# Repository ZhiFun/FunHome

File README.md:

# FunHome
DIY design of smart home hardware based on Home Assistant.
It will include a variety of DIY smart home hardware: smart lights, smart switches, various sensors, automation devices, etc., and will be continuously updated.

  a. Provides CAD files for direct 3D printing.
  
  b. Offers hardware design for PCB fabrication.
  
  c. Provides YAML configuration code for configuring corresponding functions in ESPHome.
  
  (for usage instructions, refer to:https://www.bilibili.com/video/BV14ryhYHEJK/?spm_id_from=333.999.0.0&vd_source=eef55077bd933049fd878e3b9b8782e2) 

【1】 funHomeLight：
A night light based on ESP32-C3 + WS2812 + DS18B20, capable of displaying multiple colors, various display effects, timed on/off, temperature protection, and other features.

cad: https://a360.co/3APonfi

【2】funHomeSensorTH：
The funHomeSensorTH is based on the ESP32-C3 + DHT11 and integrates temperature and humidity data acquisition functionality, with configurable reporting frequency.

cad: https://a360.co/3CE3DYF

【3】funHomeSwitch：
funHomeSwitch is composed of modules such as the ES32C3, SG90 servo, ambient light sensor, lithium battery, etc. It can be installed on a standard 86-type switch and used with Home Assistant for remote light control.

cad: https://a360.co/4gaNJ6r

【4】funHomeFan：
The funHomeFan is an intelligent small fan project based on the ESP32C3, which can be remotely controlled via a smartphone to adjust the fan speed with 3 adjustable levels.

cad: https://a360.co/4jmC1qw

【5】funHomePcController：
The funHomePcController is based on the ESP32-C3 and allows one-click remote control of a computer’s power on/off, with support for low power consumption.

cad: https://a360.co/3GjO7Dl

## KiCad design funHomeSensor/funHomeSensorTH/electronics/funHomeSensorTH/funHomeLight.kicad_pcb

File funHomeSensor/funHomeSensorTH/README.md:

The project is based on ESPHome and applied to the Home Assistant platform.

cad:
https://a360.co/3CE3DYF

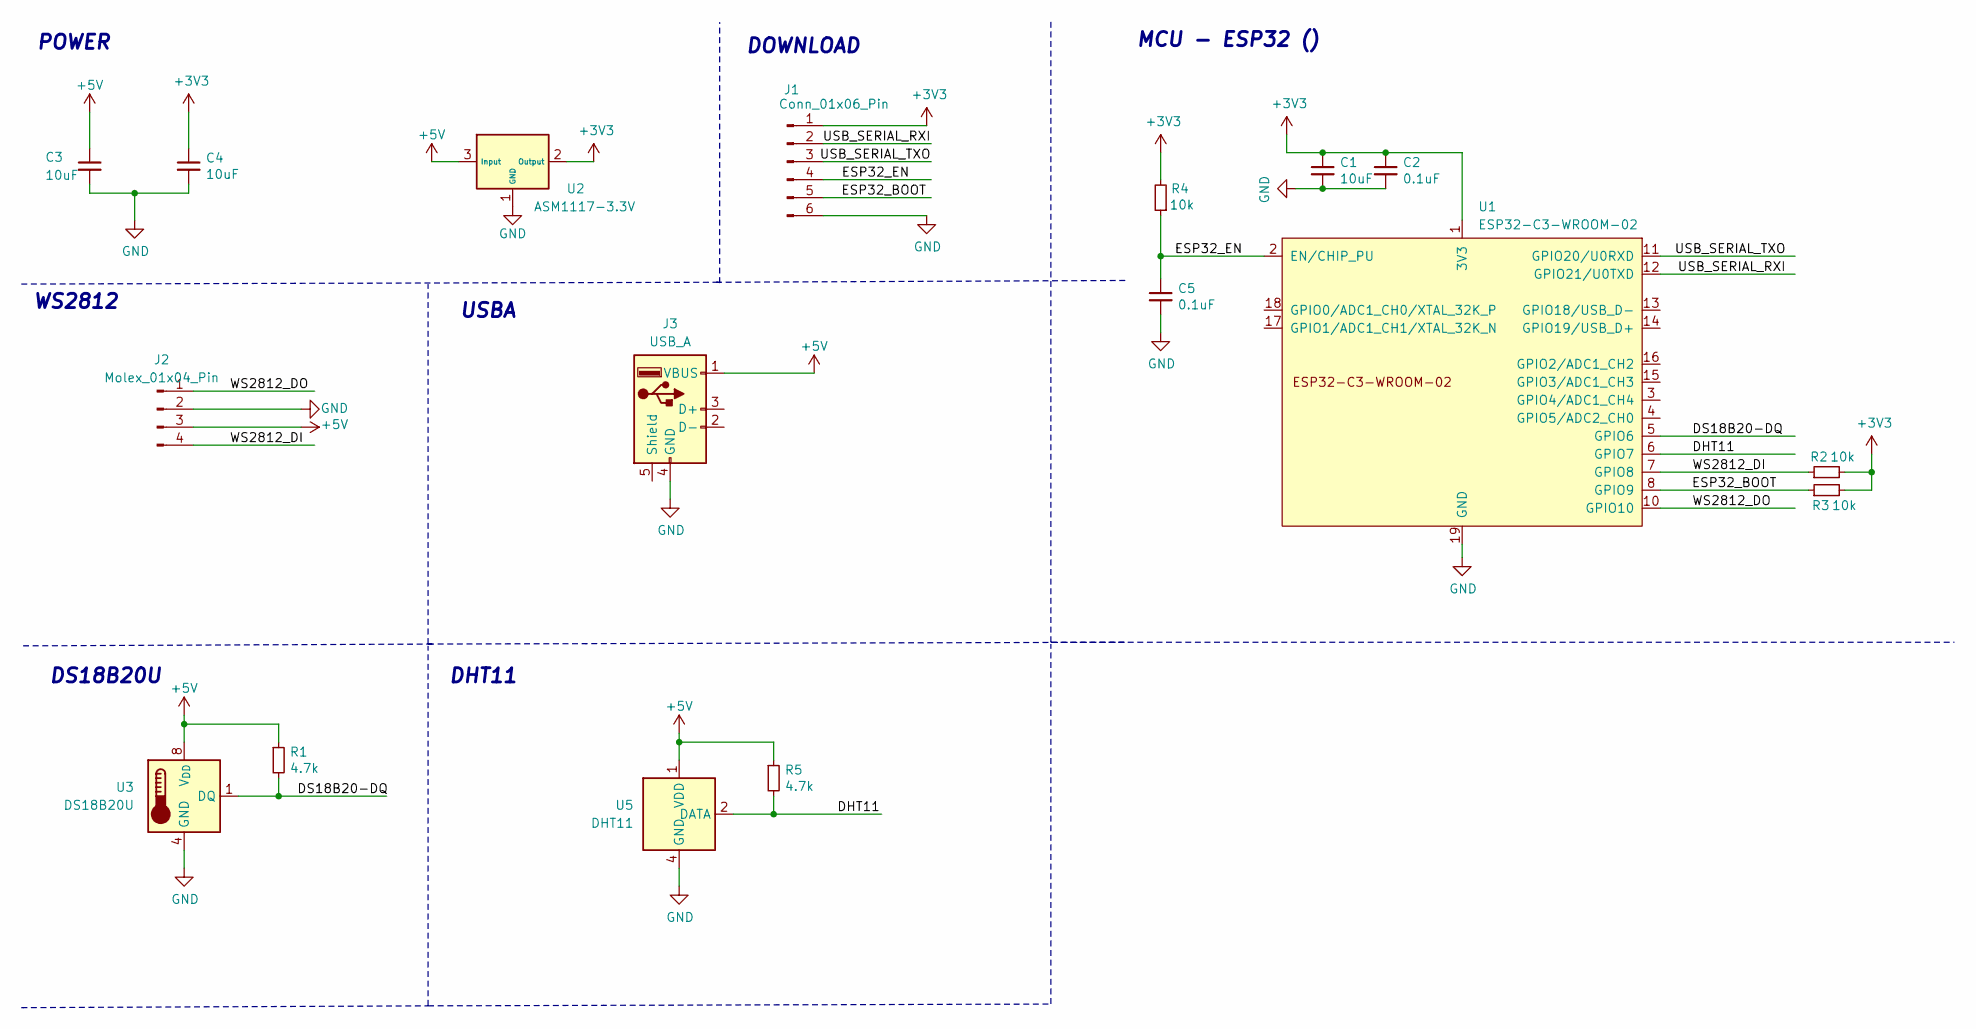
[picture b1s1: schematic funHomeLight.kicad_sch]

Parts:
C1, C3, C4: 10uF; C_0805_2012Metric; LCSC C15850
C2, C5: 0.1uF; C_0805_2012Metric; LCSC C1591
J1: Conn_01x06_Pin; JST_XH_B6B-XH-A_1x06_P2.50mm_Vertical
J2: Molex_01x04_Pin; Molex_CLIK-Mate_502382-0470_1x04-1MP_P1.25mm_Vertical
J3: USB_A; USB_A_Molex_105057_Vertical
R1, R5: 4.7k; R_0603_1608Metric; LCSC C105580
R2, R3, R4: 10k; R_0603_1608Metric; LCSC C105580
U1: ESP32-C3-WROOM-02
U2: ASM1117-3.3V; SOT-223-3_TabPin2; LCSC C6186, C35879, or others
U3: DS18B20U; MSOP-8_3x3mm_P0.65mm
U5: DHT11; Aosong_DHT11_5.5x12.0_P2.54mm

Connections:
+3V3: C1.1, C2.1, C4.1, J1.1, R2.2, R3.2, R4.2, U1.1 (3V3), U2.2 (Output)
+5V: C3.1, J2.3, J3.1 (VBUS), R1.1, R5.1, U2.3 (Input), U3.8 (V_{DD}), U5.1 (VDD)
/DHT11: R5.2, U1.6 (GPIO7), U5.2 (DATA)
/DS18B20-DQ: R1.2, U1.5 (GPIO6), U3.1 (DQ)
/ESP32_BOOT: J1.5, R3.1, U1.8 (GPIO9)
/ESP32_EN: C5.1, J1.4, R4.1, U1.2 (EN/CHIP_PU)
/USB_SERIAL_RXI: J1.2, U1.12 (GPIO21/U0TXD)
/USB_SERIAL_TXO: J1.3, U1.11 (GPIO20/U0RXD)
/WS2812_DI: J2.4, R2.1, U1.7 (GPIO8)
/WS2812_DO: J2.1, U1.10 (GPIO10)
GND: C1.2, C2.2, C3.2, C4.2, C5.2, J1.6, J2.2, J3.4 (GND), U1.9 (GND), U1.19 (GND), U2.1 (GND), U3.4 (GND), U5.4 (GND)

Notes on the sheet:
POWER
DOWNLOAD
USBA
WS2812
MCU - ESP32 ()
DHT11
DS18B20U

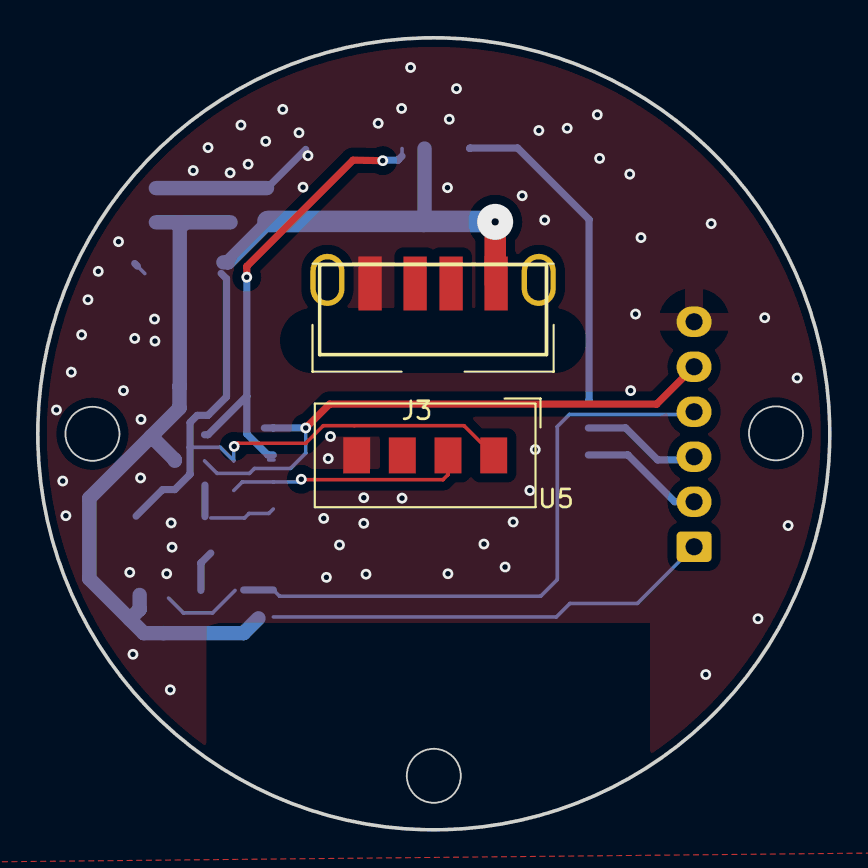
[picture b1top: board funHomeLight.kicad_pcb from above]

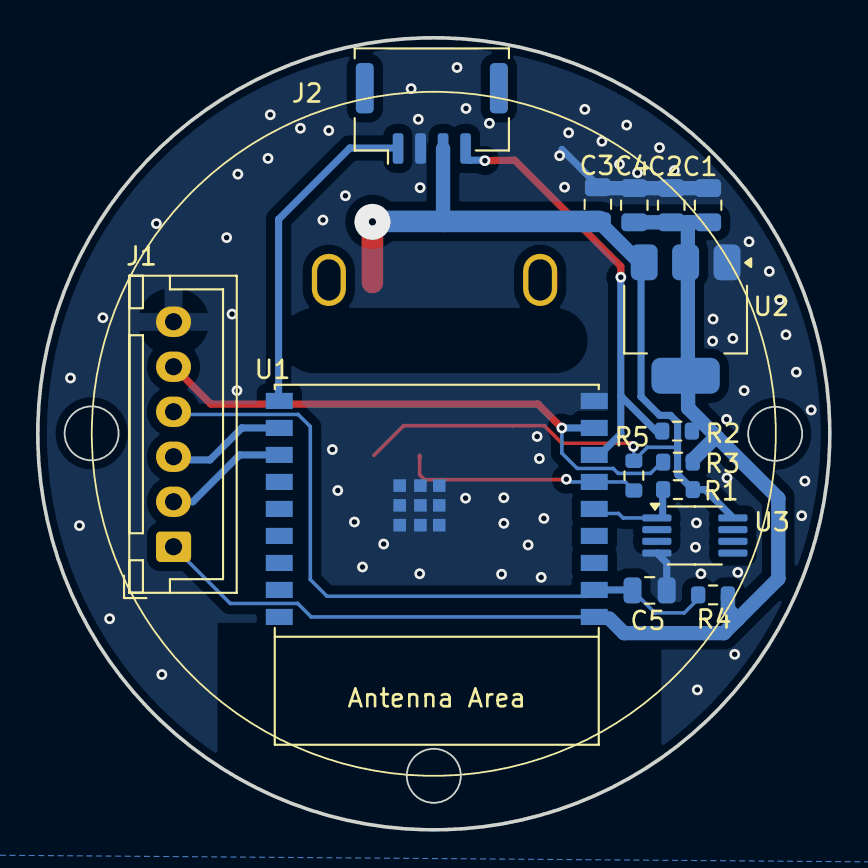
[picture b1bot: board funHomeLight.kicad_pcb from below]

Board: 2 copper layers, 44.0 x 44.0 mm, 17 parts (15 on the bottom side), 11 nets.

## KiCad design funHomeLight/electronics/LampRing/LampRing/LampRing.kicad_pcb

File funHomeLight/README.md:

The project is based on ESPHome and applied to the Home Assistant platform.

cad：
https://a360.co/3APonfi

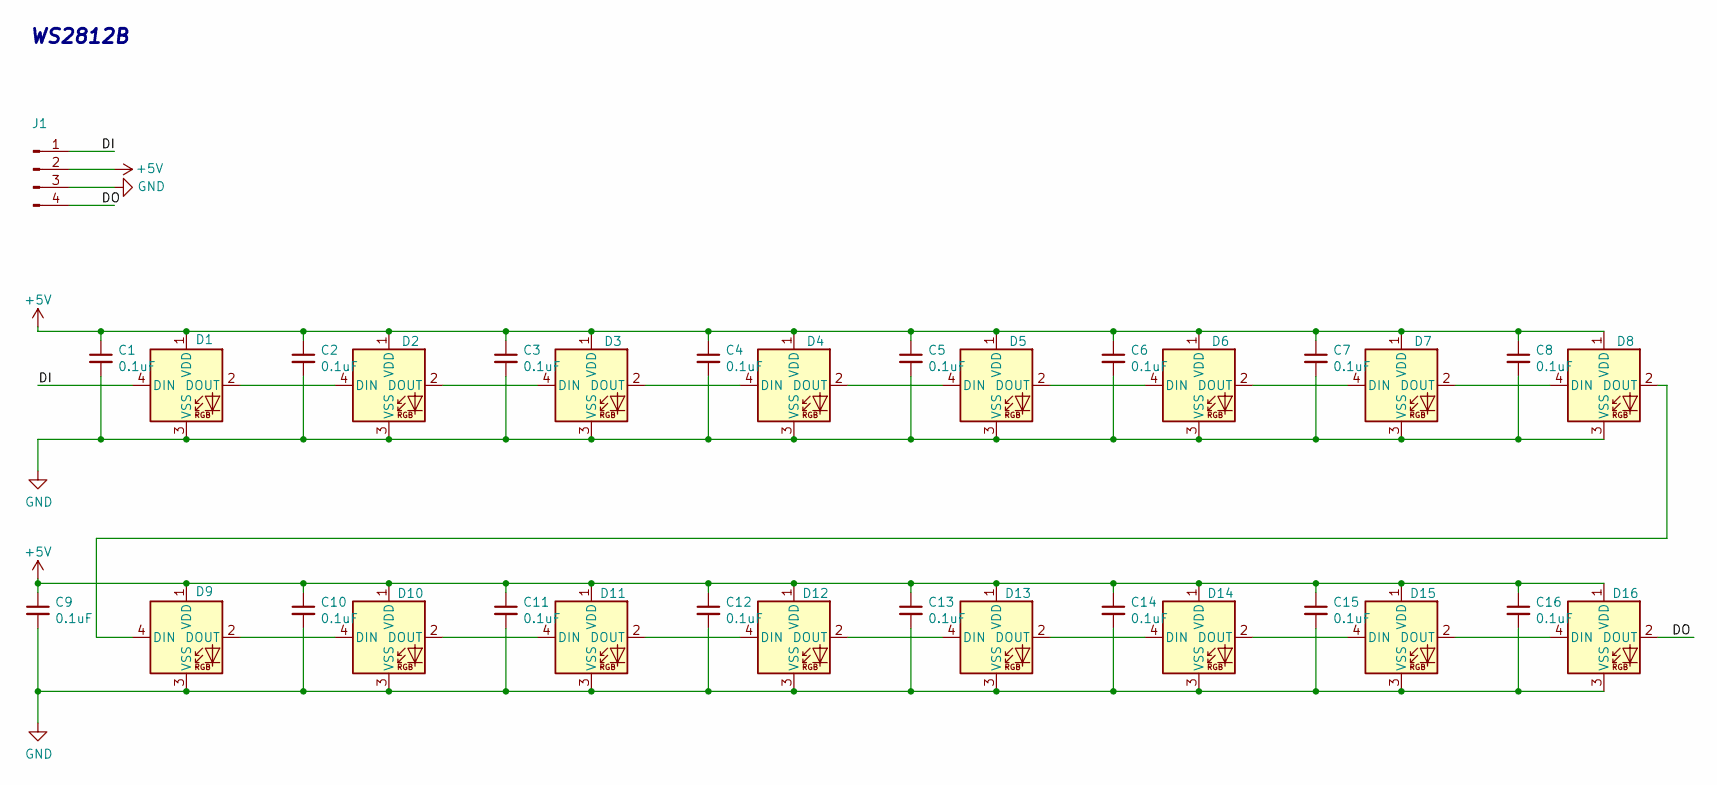
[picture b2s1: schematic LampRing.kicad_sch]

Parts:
C1, C2, C3, C4, C5, C6, C7, C8, C9, C10, C11, C12, C13, C14, C15, C16: 0.1uF; C_0603_1608Metric; LCSC C1591
D1, D2, D3, D4, D5, D6, D7, D8, D9, D10, D11, D12, D13, D14, D15, D16: LED_WS2812B_PLCC4_5.0x5.0mm_P3.2mm
J1: PinHeader_1x04_P2.00mm_Vertical

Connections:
+5V: C1.1, C2.1, C3.1, C4.1, C5.1, C6.1, C7.1, C8.1, C9.1, C10.1, C11.1, C12.1, C13.1, C14.1, C15.1, C16.1, D1.1 (VDD), D2.1 (VDD), D3.1 (VDD), D4.1 (VDD), D5.1 (VDD), D6.1 (VDD), D7.1 (VDD), D8.1 (VDD), D9.1 (VDD), D10.1 (VDD), D11.1 (VDD), D12.1 (VDD), D13.1 (VDD), D14.1 (VDD), D15.1 (VDD), D16.1 (VDD), J1.2
/DI: D1.4 (DIN), J1.1
/DO: D16.2 (DOUT), J1.4
GND: C1.2, C2.2, C3.2, C4.2, C5.2, C6.2, C7.2, C8.2, C9.2, C10.2, C11.2, C12.2, C13.2, C14.2, C15.2, C16.2, D1.3 (VSS), D2.3 (VSS), D3.3 (VSS), D4.3 (VSS), D5.3 (VSS), D6.3 (VSS), D7.3 (VSS), D8.3 (VSS), D9.3 (VSS), D10.3 (VSS), D11.3 (VSS), D12.3 (VSS), D13.3 (VSS), D14.3 (VSS), D15.3 (VSS), D16.3 (VSS), J1.3
unnamed: D1.2 (DOUT), D2.4 (DIN)
unnamed: D2.2 (DOUT), D3.4 (DIN)
unnamed: D3.2 (DOUT), D4.4 (DIN)
unnamed: D4.2 (DOUT), D5.4 (DIN)
unnamed: D5.2 (DOUT), D6.4 (DIN)
unnamed: D6.2 (DOUT), D7.4 (DIN)
unnamed: D7.2 (DOUT), D8.4 (DIN)
unnamed: D8.2 (DOUT), D9.4 (DIN)
unnamed: D9.2 (DOUT), D10.4 (DIN)
unnamed: D10.2 (DOUT), D11.4 (DIN)
unnamed: D11.2 (DOUT), D12.4 (DIN)
unnamed: D12.2 (DOUT), D13.4 (DIN)
unnamed: D13.2 (DOUT), D14.4 (DIN)
unnamed: D14.2 (DOUT), D15.4 (DIN)
unnamed: D15.2 (DOUT), D16.4 (DIN)

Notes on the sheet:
WS2812B

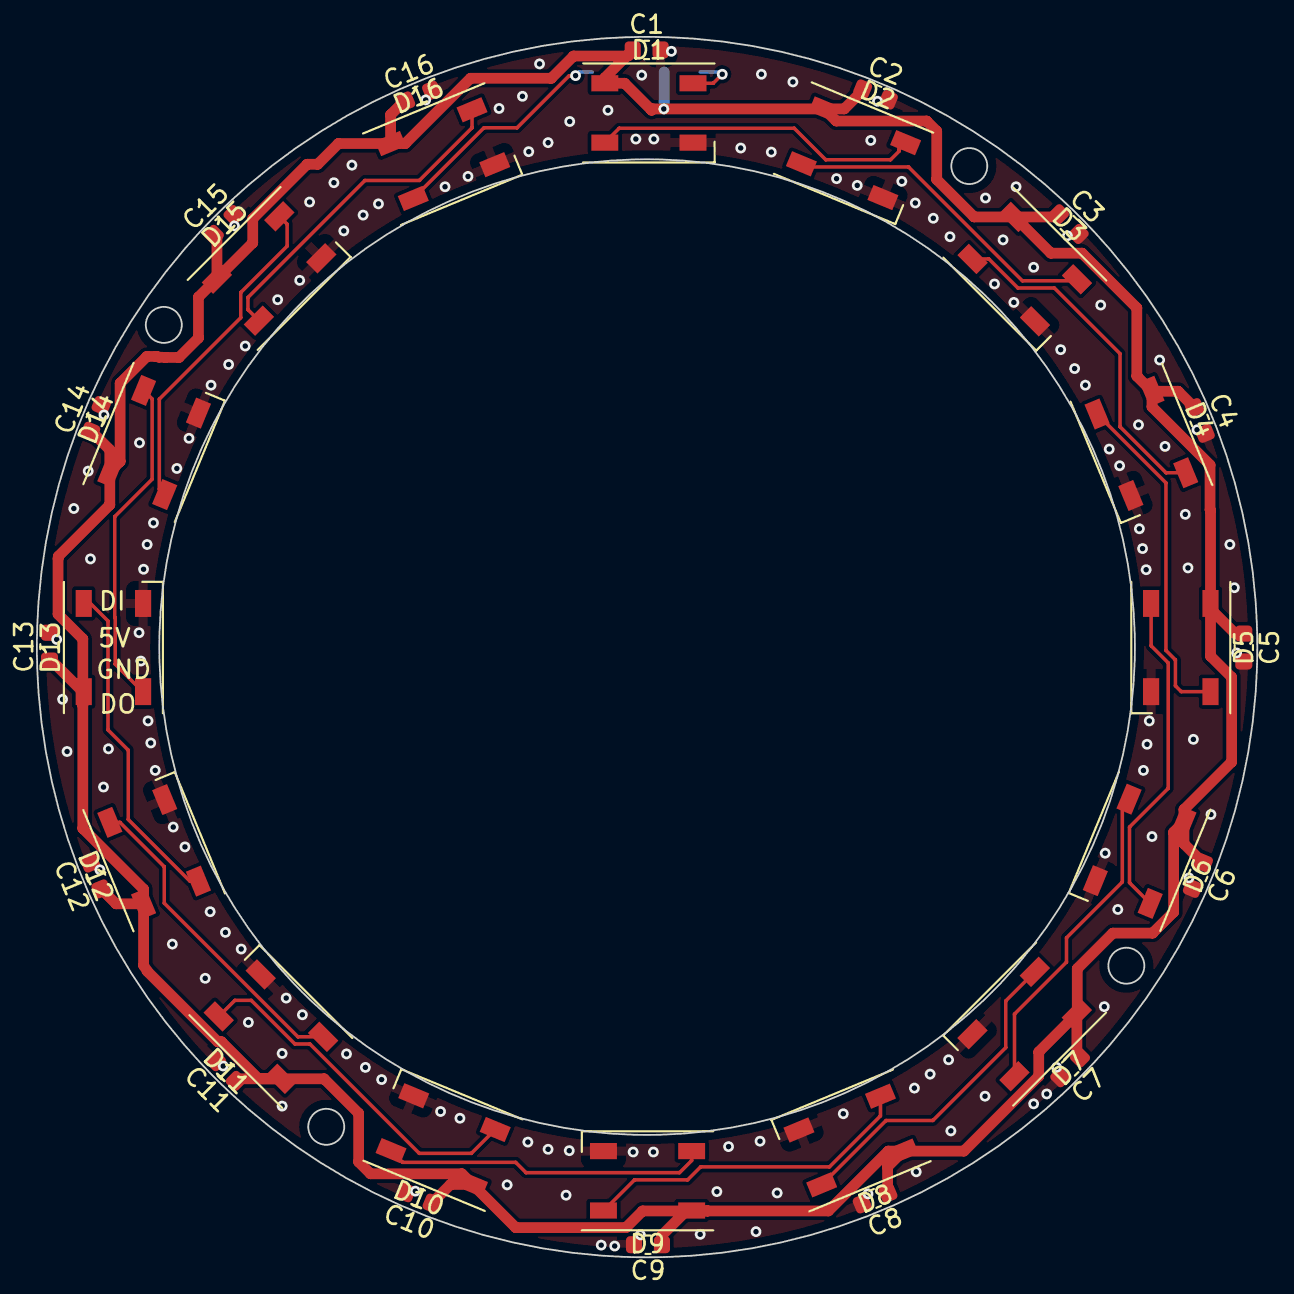
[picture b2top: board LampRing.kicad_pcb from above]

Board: 2 copper layers, 67.8 x 67.8 mm, 33 parts (1 on the bottom side), 19 nets.

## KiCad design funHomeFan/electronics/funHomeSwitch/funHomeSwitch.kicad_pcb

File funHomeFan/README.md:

cad：
https://a360.co/4jmC1qw
https://a360.co/4kkfUlO
https://a360.co/3FCmd4W

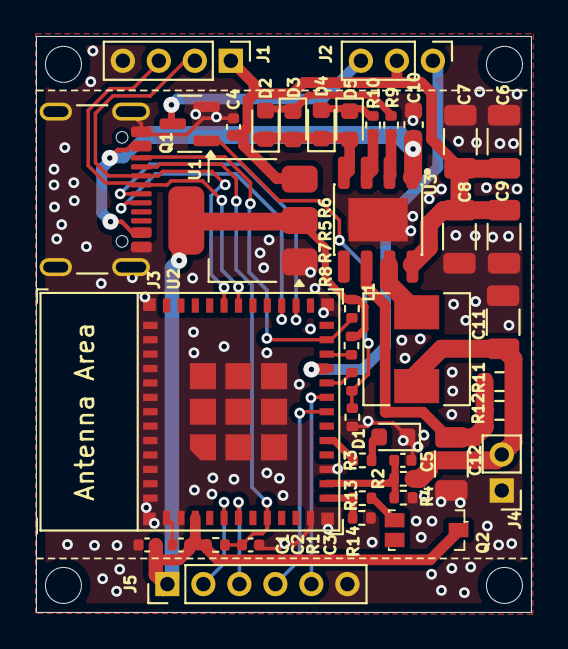
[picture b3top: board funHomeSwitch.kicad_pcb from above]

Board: 2 copper layers, 27.5 x 32.0 mm, 42 parts (0 on the bottom side), 32 nets.

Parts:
C1, C4: 10uF; C_0402_1005Metric
C2, C3, C5: 0.1uF; C_0402_1005Metric
C6, C7, C8, C9, C11, C12: 22uF; C_1206_3216Metric
C10: 10uF; C_0603_1608Metric
D1, D2, D3, D4, D5: LED; LED_0603_1608Metric
J1: Conn_01x04_Pin; PinHeader_1x04_P2.00mm_Vertical
J2: PinHeader_1x03_P2.00mm_Vertical
J3: USB_C_Receptacle_USB2.0_16P; USB_C_Receptacle_GCT_USB4105-xx-A_16P_TopMnt_Horizontal
J4: PinHeader_1x02_P2.00mm_Vertical
J5: Conn_01x06_Pin; PinHeader_1x06_P2.00mm_Vertical
L1: L; L_Chilisin_BMRA00050530
Q1: AO3400A; SOT-23
Q2: TEMT6000X01; Phototransistor_SMD_4x2mm_TEMT6000X01
R1, R2, R4, R5, R6, R8, R13, R14: 10k; R_0402_1005Metric
R3: 150R; R_0402_1005Metric
R7: 100R; R_0402_1005Metric
R9, R10: 2K; R_0402_1005Metric
R11, R12: 1R; R_0603_1608Metric
U1: ASM1117-3.3V; SOT-223-3_TabPin2
U2: ESP32-C3-MINI-1
U3: IP5306; SOIC9P127_490X600X170L84X42T330X241N

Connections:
+3V3: C1.1, C2.1, J5.1, Q2.1 (C), R1.2, R5.2, R6.2, U1.2 (Output), U2.3 (3V3)
+5V: C4.1, C6.1, C7.1, C8.1, C9.1, J1.1, J2.2, U1.3 (Input), U3.8 (VOUT)
/BAT+: C11.1, J4.2, L1.2, R2.1, R11.2, R12.2
/ESP32_BOOT: J3.B8 (SBU2), R6.1, U2.23 (GPIO9)
/ESP32_EN: C3.1, J3.A5 (CC1), R1.1, U2.8 (EN/CHIP_PU)
/GPIO2: J5.2, U2.5 (GPIO2/ADC1_CH2)
/GPIO3: J5.3, U2.6 (GPIO3/ADC1_CH3)
/GPIO4: J5.4, U2.18 (GPIO4/ADC1_CH4)
/GPIO5: J5.5, U2.19 (GPIO5/ADC2_CH0)
/LED_CTRL: R3.1, U2.16 (GPIO10)
/LSensorIO: R13.1, R14.1, U2.12 (GPIO0/ADC1_CH0/XTAL_32K_P)
/SG90_POWER: R7.1, U2.20 (GPIO6)
/SG90_PWM: J2.1, U2.21 (GPIO7)
/USBD+: J3.B6 (D+), U2.27 (GPIO19/USB_D+)
/USBD-: J3.A7 (D-), U2.26 (GPIO18/USB_D-)
/USB_SERIAL_RXI: J1.2, J3.B7 (D-), U2.31 (GPIO21/U0TXD)
/USB_SERIAL_TXO: J1.3, J3.A6 (D+), U2.30 (GPIO20/U0RXD)
/VIN_5V: C10.2, J3.A4 (VBUS), J3.A9 (VBUS), J3.B4 (VBUS), J3.B9 (VBUS), U3.1 (VCC)
GND: C1.2, C2.2, C3.2, C4.2, C5.1, C6.2, C7.2, C8.2, C9.2, C10.1, C11.2, C12.2, D1.1 (K), J1.4, J3.A1 (GND), J3.A12 (GND), J3.B1 (GND), J3.B12 (GND), J3.S1 (SHIELD), J4.1, J5.6, Q1.2 (S), R4.2, R8.2, R14.2, U1.1 (GND), U2.1 (GND), U2.2 (GND), U2.11 (GND), U2.14 (GND), U2.36 (GND), U2.37 (GND), U2.38 (GND), U2.39 (GND), U2.40 (GND), U2.41 (GND), U2.42 (GND), U2.43 (GND), U2.44 (GND), U2.45 (GND), U2.46 (GND), U2.47 (GND), U2.48 (GND), U2.49 (GND), U2.50 (GND), U2.51 (GND), U2.52 (GND), U2.53 (GND), U3.9 (GND)
unnamed: D1.2 (A), R3.2
unnamed: D2.2 (A), D3.1 (K), R9.2
unnamed: D2.1 (K), D3.2 (A), D4.1 (K), D5.2 (A), U3.4 (LED3)
unnamed: D4.2 (A), D5.1 (K), R10.2
unnamed: J2.3, Q1.3 (D)
unnamed: Q1.1 (G), R7.2, R8.1
unnamed: Q2.2 (E), R13.2
unnamed: C5.2, R2.2, R4.1, U2.13 (GPIO1/ADC1_CH1/XTAL_32K_N)
unnamed: R5.1, U2.22 (GPIO8)
unnamed: C12.1, R11.1, R12.1, U3.6 (BAT)
unnamed: R9.1, U3.2 (LED1)
unnamed: R10.1, U3.3 (LED2)
unnamed: L1.1, U3.7 (SW)

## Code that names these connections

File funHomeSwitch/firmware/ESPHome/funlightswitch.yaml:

# captive_portal:
  
# sensor:
# # 光照传感器配置
#   - platform: adc
#     pin: GPIO0
#     id: temt6000_sensor
#     name: "TEMT6000 Illuminance"
#     device_class: illuminance
#     unit_of_measurement: lx
#     update_interval: 24h
#     attenuation: 12db
#     filters:
#       - lambda: |-
#           return (x / 10000.0) * 2000000.0;

# LED 控制配置
output:
  - platform: gpio
    pin: GPIO10
    id: gpio10_led

# 舵机 PWM 输出配置
  - platform: ledc
    pin: GPIO7
    frequency: 50Hz
    id: pwm_output

# 舵机控制配置
servo:
  - id: sg90_servo
    output: pwm_output
    min_level: 2.5%  # 调整最小脉宽信号
    max_level: 12.5%  # 调整最大脉宽信号

# 舵机逻辑开关
switch:
  - platform: template
    name: "SG90 Servo Control Switch"
    id: sg90_servo_switch  # 修复：定义 ID
    turn_on_action:
      - output.turn_on: pwm_output # 打开PWM    
      - switch.turn_on: sg90_power  # 打开 GPIO6
      - delay: 100ms  # 确保电源已开启   
      - output.turn_on: gpio10_led  # 打开 GPIO10 LED
      - delay: 50ms  # 闪烁持续时间
      - output.turn_off: gpio10_led # 关闭 GPIO10 LED       
      - servo.write:
          id: sg90_servo
          level: !lambda 'return 0.3;'   
      - delay: 200ms  # 保持位置 200 毫秒
      - servo.write:
          id: sg90_servo
          level: !lambda 'return 0;'    # 恢复到中间
      - delay: 200ms               
      - switch.turn_off: sg90_power  # 关闭 GPIO6
      - output.turn_off: pwm_output  # 关闭PWM

    turn_off_action:
      - output.turn_on: pwm_output # 打开PWM
      - switch.turn_on: sg90_power  # 打开 GPIO6               
      - delay: 100ms  # 确保电源已开启
      - output.turn_on: gpio10_led  # 打开 GPIO10 LED
      - delay: 50ms  # 闪烁持续时间
      - output.turn_off: gpio10_led # 关闭 GPIO10 LED
      - servo.write:
          id: sg90_servo
          level: !lambda 'return -0.3;'
      - delay: 200ms  # 保持位置 200 毫秒
      - servo.write:
          id: sg90_servo
          level: !lambda 'return 0;'    # 恢复到中间
      - delay: 200ms             
      - switch.turn_off: sg90_power  # 关闭 GPIO6
      - output.turn_off: pwm_output  # 关闭PWM

  - platform: gpio
    pin: GPIO6
    id: sg90_power
    name: "SG90 Power"

# 内部变量
globals:
  - id: pre_action_illuminance
    type: float
    restore_value: no
    initial_value: '0.0'

# # 设置 ESP32 进入低功耗模式
# deep_sleep:
#   id: deep_sleep_1
#   run_duration: 5s
#   sleep_duration: 5s

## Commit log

2024-11-14 add funHomeLight to the project
2024-11-14 add FunHomeLight rendering
2024-11-15 modify funHomeLight cad: Base.step
2024-11-19 modify funHomeLight/README.md
2024-11-22 modify
2024-11-22 add funHomeSensorTH to the project
2024-11-22 add doc to funHomeSensorTH
2025-02-16 add funHomeSwitch to the project
2025-05-28 add funHomeFan to the project
2025-06-29 add funHomePcController
2025-06-29 add README.md for funHomePcController
